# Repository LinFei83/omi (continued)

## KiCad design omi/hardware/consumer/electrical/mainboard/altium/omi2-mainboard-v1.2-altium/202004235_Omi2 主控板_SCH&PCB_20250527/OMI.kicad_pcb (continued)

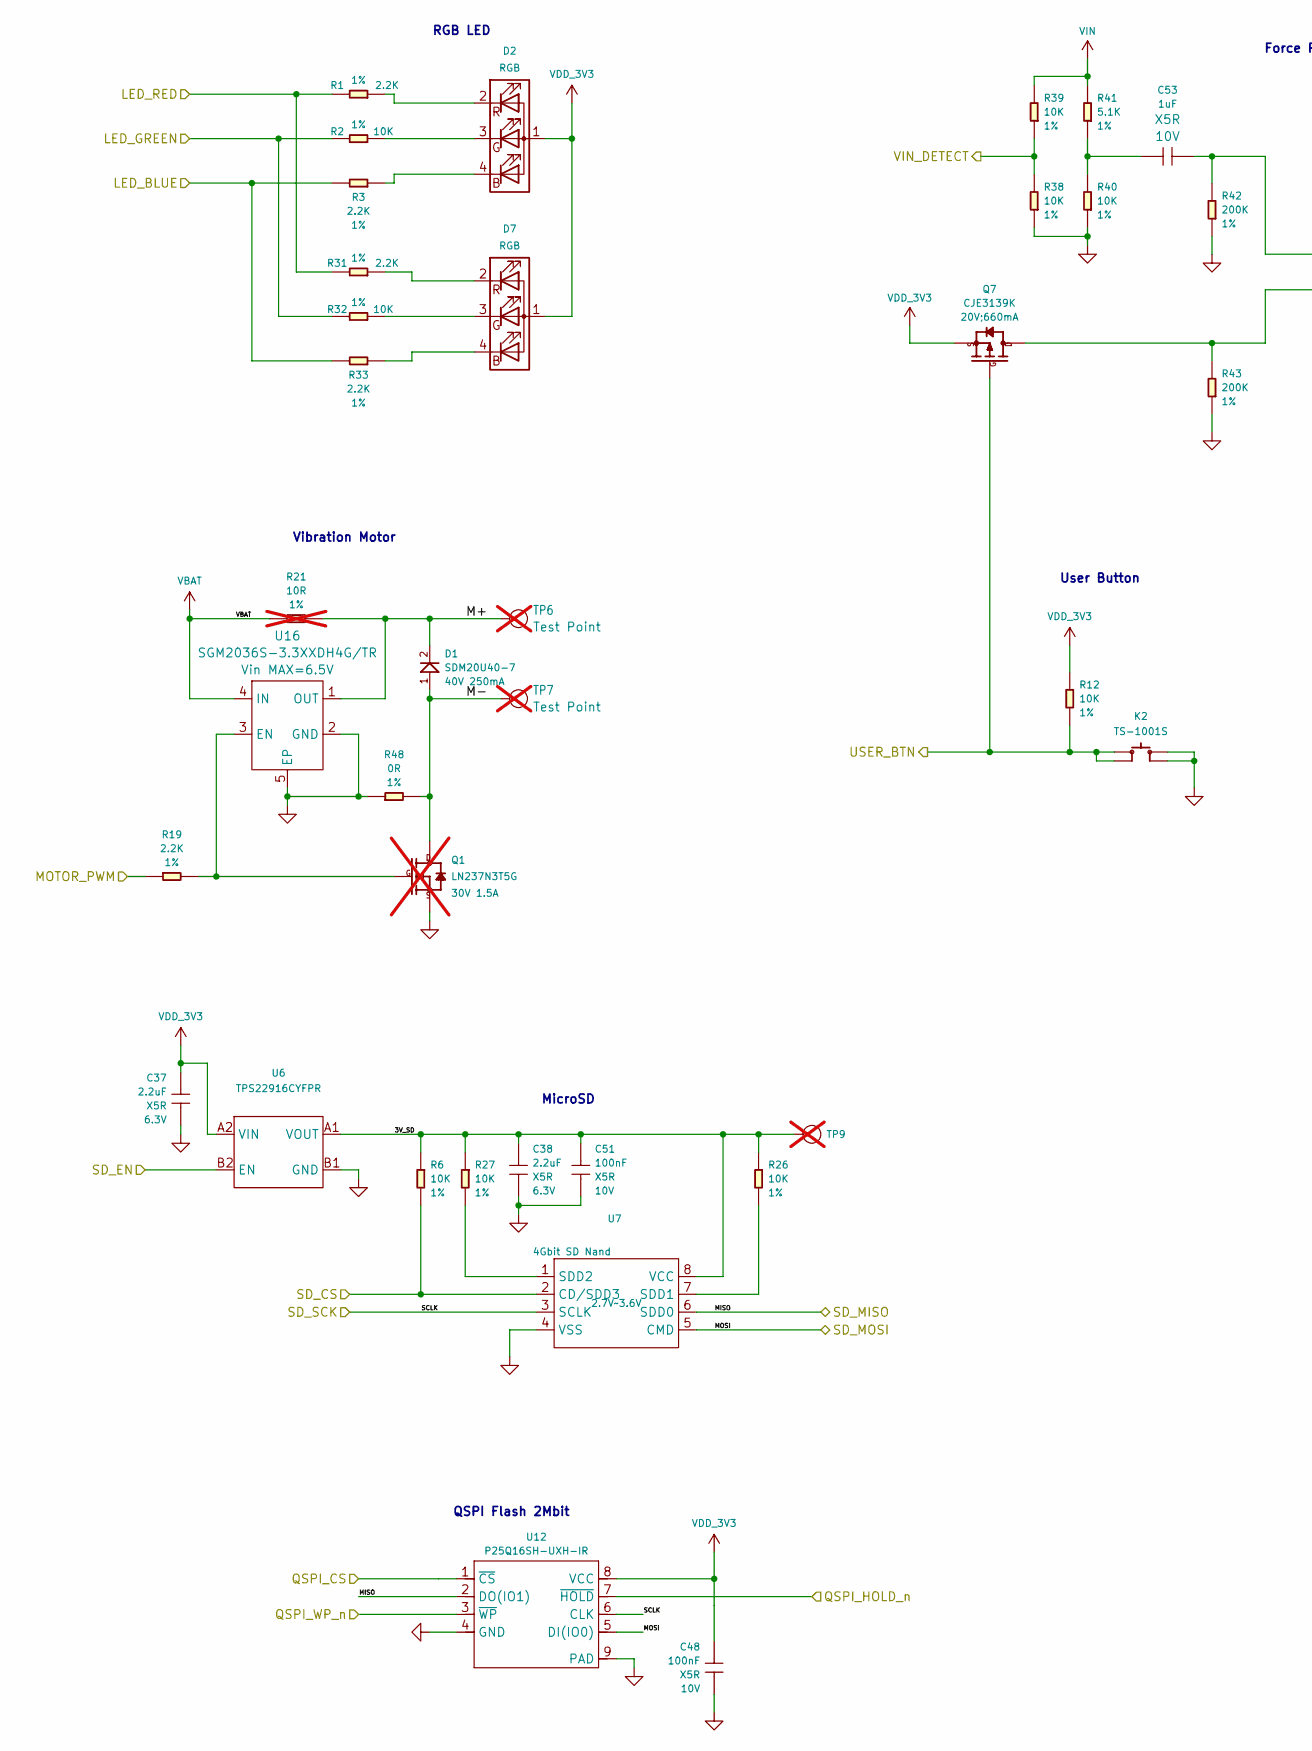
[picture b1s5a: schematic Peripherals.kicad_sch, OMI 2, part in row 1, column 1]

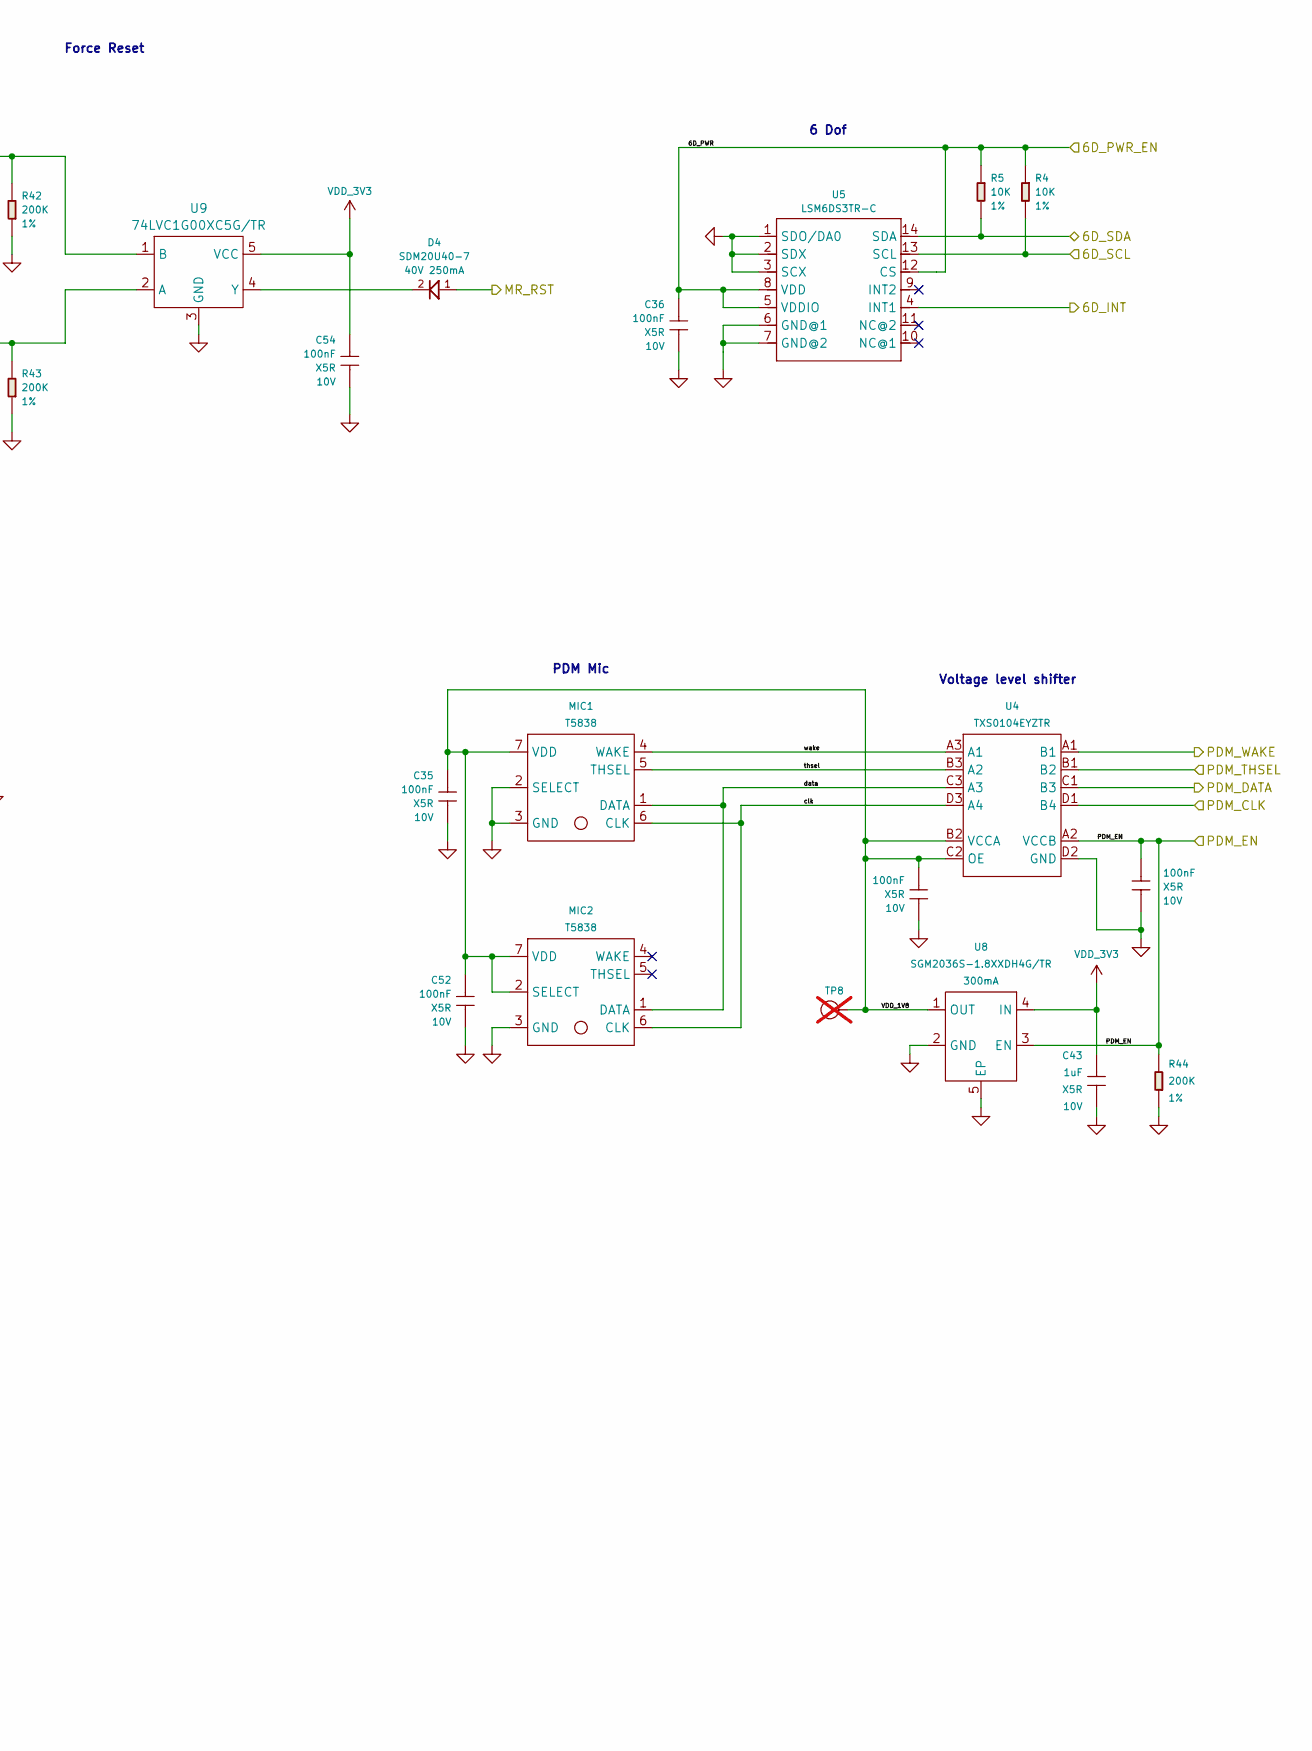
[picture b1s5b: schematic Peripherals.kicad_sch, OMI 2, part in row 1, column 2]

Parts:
C35, C36, C39, C40, C48, C51, C52, C54: 100nF; C0201; Voltage Rating 10V; MPN CC0201KRX5R6BB104
C37, C38: 2.2uF; C0201; Voltage Rating 6.3V; MPN 0201X225M6R3NT
C43, C53: 1uF; C0201; Voltage Rating 10V; MPN GRM033R61A105ME44D
D1, D4: SDM20U40-7; SOD-523; Rating 40V 250mA; MPN SDM20U40-7
D2, D7: RGB; SMD-LED-RGB-0.7X0.7X0.5MM; MPN MHPA0606RGBDT
K2: TS-1001S; SW4-SMD-2.8-2.6X1.6X0.53MM; MPN TS-1001S
MIC1, MIC2: T5838; MIC7P_0d8_3_5x2_65x0_98mm; MPN MMICT5838-00-012
Q1: LN237N3T5G; PMOS_1.0X0.6X0.35MM; Rating 30V 1.5A; MPN LN237N3T5G; not fitted
Q7: CJE3139K; SOT-523; Rating 20V;660mA; MPN CJE3139K
R1, R3, R19, R31, R33: 2.2K; R0201; Power Rating 1%; MPN RC0201FR-072K2L
R2, R4, R5, R6, R12, R26, R27, R32, R38, R39, R40: 10K; R0201; Power Rating 1%; MPN RC0201FR-0710KL
R21: 10R; R0603; Power Rating 1%; MPN RC0603FR-0710RL; not fitted
R41: 5.1K; R0201; Power Rating 1%; MPN RC0201FR-075K1L
R42, R43, R44: 200K; R0201; Power Rating 1%; MPN RC0201FR-07200KL
R48: 0R; R0201; Power Rating 1%; MPN RC0201FR-070RL
TP6, TP7: Test Point; TP-1.5X0.9MM; MPN GA30-PG05; not fitted
TP8, TP9: Test Point; TP-1X0.9MM; Part Type Test Point; not fitted
U4: TXS0104EYZTR; DSBGA12_0d5_1_89x1_39x0_625mm; MPN TXS0104EYZTR
U5: LSM6DS3TR-C; LGA14-0.5-2.5X3X0.86MM; MPN LSM6DS3TR-C
U6: TPS22916CYFPR; WLCSP4-0.4-0.77X0.77X0.33MM; MPN TPS22916CYFPR
U7: 4Gbit SD Nand; LGA8_1d27_8x6x0_85mm; Rating 2.7V~3.6V; MPN CSNP4GCR01-DPW
U8: SGM2036S-1.8XXDH4G/TR; X2SON4-0.625-1x1x0.6mm; Rating 300mA; MPN SGM2036S-1.8XXDH4G/TR
U9: 74LVC1G00XC5G/TR; SC70-5; MPN 74LVC1G00XC5G/TR
U12: P25Q16SH-UXH-IR; USON8-0.5-3X2MM; MPN P25Q16SH-UXH-IR
U16: SGM2036S-3.3XXDH4G/TR; X2SON4-0.625-1x1x0.6mm; Rating Vin MAX=6.5V; MPN SGM2036S-3.3XXDH4G/TR

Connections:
/nRF5340/P0.10/TRACEDATA1: U12.7 (~HOLD); also elsewhere on the board
/nRF5340/P0.11/TRACEDATA0: U12.1 (~CS); also elsewhere on the board
/nRF5340/P0.19: U12.3 (~WP); also elsewhere on the board
/nRF5340/P0.20: R3.2, R33.2; also elsewhere on the board
/nRF5340/P0.21: R2.2, R32.2; also elsewhere on the board
/nRF5340/P0.22: R1.2, R31.2; also elsewhere on the board
/nRF5340/P0.25/AIN4: R19.1; also elsewhere on the board
/nRF5340/P0.26/AIN5: K2.1 (A0), K2.2 (A1), Q7.1 (G), R12.2; also elsewhere on the board
/nRF5340/P1.00: U4.C1 (B3); also elsewhere on the board
/nRF5340/P1.01: U4.D1 (B4); also elsewhere on the board
/nRF5340/P1.02/TWI: U4.A1 (B1); also elsewhere on the board
/nRF5340/P1.04: C40.2, R44.2, U4.A2 (VCCB), U8.3 (EN); also elsewhere on the board
/nRF5340/P1.05: U4.B1 (B2); also elsewhere on the board
/nRF5340/P1.06: R38.2, R39.1; also elsewhere on the board
/nRF5340/P1.07: U7.3 (SCLK), U12.6 (CLK); also elsewhere on the board
/nRF5340/P1.08: U7.6 (SDD0), U12.2 (DO(IO1)); also elsewhere on the board
/nRF5340/P1.09: U7.5 (CMD), U12.5 (DI(IO0)); also elsewhere on the board
/nRF5340/P1.10: U6.B2 (EN); also elsewhere on the board
/nRF5340/P1.11: R6.2, U7.2 (CD/SDD3); also elsewhere on the board
/nRF5340/P1.12: C36.2, R4.1, R5.1, U5.5 (VDDIO), U5.8 (VDD), U5.12 (CS); also elsewhere on the board
/nRF5340/P1.13: U5.4 (INT1); also elsewhere on the board
/nRF5340/P1.14: R4.2, U5.13 (SCL); also elsewhere on the board
/nRF5340/P1.15: R5.2, U5.14 (SDA); also elsewhere on the board
/nRF5340/Peripherals/3V_SD: C38.2, C51.2, R6.1, R26.1, R27.1, TP9.1 (T), U6.A1 (VOUT), U7.8 (VCC)
/nRF5340/Peripherals/M+: D1.2, R21.2, TP6.1 (T), U16.1 (OUT)
/nRF5340/Peripherals/M-: D1.1, Q1.3 (D), R48.2, TP7.1 (T)
/nRF5340/Peripherals/VDD_1V8: C35.2, C39.2, C52.2, MIC1.7 (VDD), MIC2.2 (SELECT), MIC2.7 (VDD), TP8.1 (T), U4.B2 (VCCA), U4.C2 (OE), U8.1 (OUT)
/nRF5340/Peripherals/clk: MIC1.6 (CLK), MIC2.6 (CLK), U4.D3 (A4)
/nRF5340/Peripherals/data: MIC1.1 (DATA), MIC2.1 (DATA), U4.C3 (A3)
/nRF5340/Peripherals/thsel: MIC1.5 (THSEL), U4.B3 (A2)
/nRF5340/Peripherals/wake: MIC1.4 (WAKE), U4.A3 (A1)
/nRF5340/~RESET: D4.1; also elsewhere on the board
GND: C35.1, C36.1, C37.1, C38.1, C39.1, C40.1, C43.1, C48.1, C51.1, C52.1, C54.1, K2.3 (B0), K2.4 (B1), MIC1.2 (SELECT), MIC1.3 (GND), MIC2.3 (GND), Q1.2 (S), R38.1, R40.1, R42.1, R43.1, R44.1, R48.1, U4.D2 (GND), U5.1 (SDO/DA0), U5.2 (SDX), U5.3 (SCX), U5.6 (GND@1), U5.7 (GND@2), U6.B1 (GND), U7.4 (VSS), U8.2 (GND), U8.5 (EP), U9.3 (GND), U12.4 (GND), U12.9 (PAD), U16.2 (GND), U16.5 (EP); also elsewhere on the board
unnamed: C53.1, R40.2, R41.1
unnamed: D2.4 (BK), R3.1
unnamed: D2.3 (GK), R2.1
unnamed: D2.2 (RK), R1.1
unnamed: D7.4 (BK), R33.1
unnamed: D7.3 (GK), R32.1
unnamed: D7.2 (RK), R31.1
unnamed: Q1.1 (G), R19.2, U16.3 (EN)
unnamed: Q7.3 (D), R43.2, U9.2 (A)
unnamed: R26.2, U7.7 (SDD1)
unnamed: R27.2, U7.1 (SDD2)
unnamed: C53.2, R42.2, U9.1 (B)
unnamed: D4.2, U9.4 (Y)
VBAT: R21.1, U16.4 (IN); also elsewhere on the board
VDD_3V3: C37.2, C43.2, C48.2, C54.2, D2.1 (A), D7.1 (A), Q7.2 (S), R12.1, U6.A2 (VIN), U8.4 (IN), U9.5 (VCC), U12.8 (VCC); also elsewhere on the board
VIN: R39.2, R41.2; also elsewhere on the board

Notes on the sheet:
Force Reset
RGB LED
6 Dof
QSPI Flash 2Mbit
Vibration Motor
PDM Mic
User Button
MicroSD
Voltage level shifter

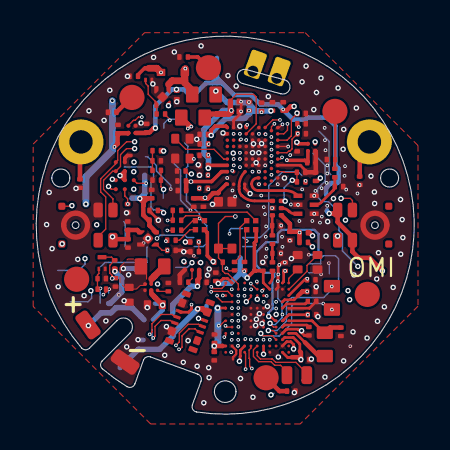
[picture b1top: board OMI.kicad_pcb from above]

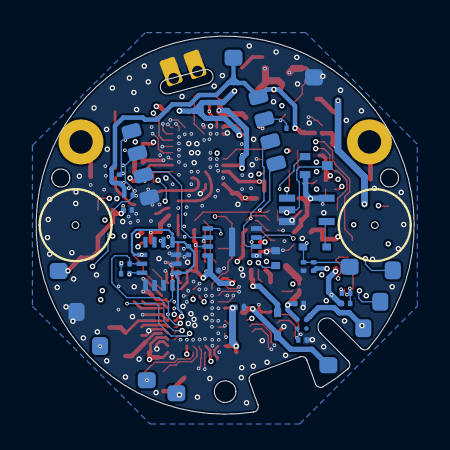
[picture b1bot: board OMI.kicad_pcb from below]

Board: 4 copper layers, 21.0 x 21.0 mm, 162 parts (36 on the bottom side), 118 nets.

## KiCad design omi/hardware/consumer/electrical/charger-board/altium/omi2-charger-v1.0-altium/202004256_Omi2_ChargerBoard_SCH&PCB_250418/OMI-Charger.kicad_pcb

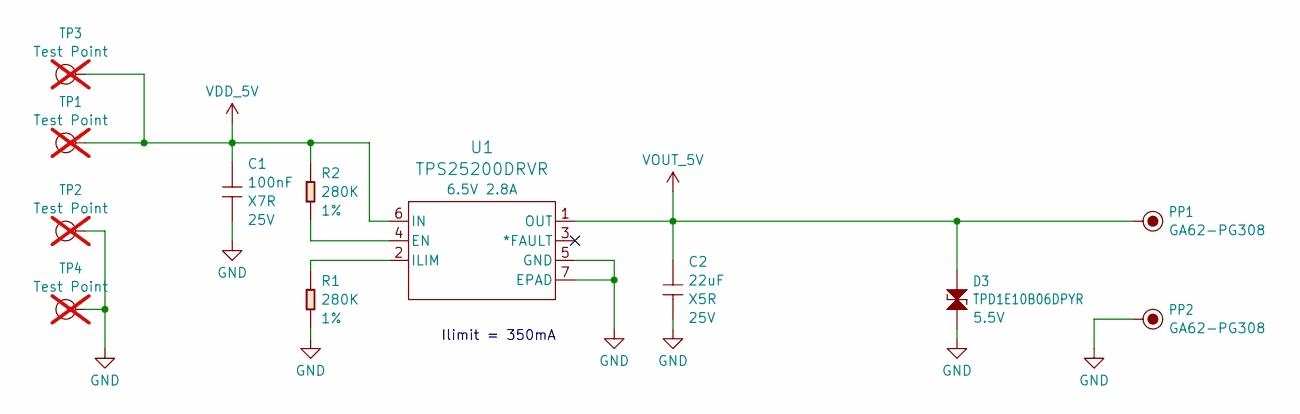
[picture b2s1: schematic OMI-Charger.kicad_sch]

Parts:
C1: 100nF; C0402; Voltage Rating 25V; MPN CC0402KRX7R8BB104
C2: 22uF; C0805; Voltage Rating 25V; MPN CC0805MKX5R8BB226
D3: TPD1E10B06DPYR; ESD-0402; Rating 5.5V; MPN TPD1E10B06DPYR
PP1, PP2: GA62-PG308; POGOPIN1_2.3X2.3X4MM; MPN GA62-PG308
R1, R2: 280K; R0402; Power Rating 1%; MPN RC0402FR-07280KL
TP1, TP2, TP3, TP4: Test Point; TP-80X40MIL; Part Type Test Point; not fitted
U1: TPS25200DRVR; DRV6-0.65-2x2x0.8mm; Rating 6.5V 2.8A; MPN TPS25200DRVR

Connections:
GND: C1.2, C2.2, D3.1, PP2.1 (T), R1.2, TP2.1 (T), TP4.1 (T), U1.5 (GND), U1.7 (EPAD)
unnamed: R2.2, U1.4 (EN)
unnamed: R1.1, U1.2 (ILIM)
VDD_5V: C1.1, R2.1, TP1.1 (T), TP3.1 (T), U1.6 (IN)
VOUT_5V: C2.1, D3.2, PP1.1 (T), U1.1 (OUT)

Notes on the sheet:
Ilimit = 350mA

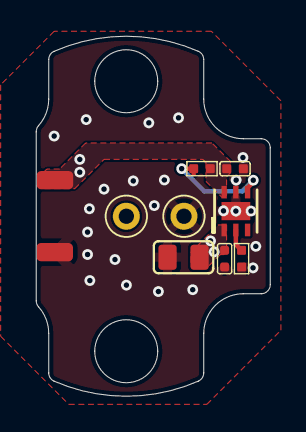
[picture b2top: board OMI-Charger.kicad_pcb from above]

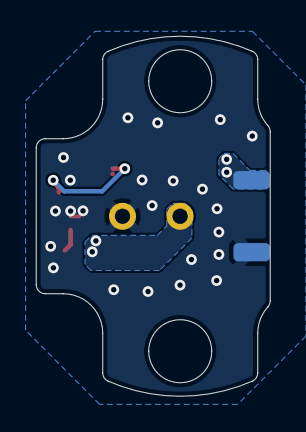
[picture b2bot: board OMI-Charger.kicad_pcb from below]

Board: 2 copper layers, 13.0 x 20.0 mm, 12 parts (2 on the bottom side), 5 nets.

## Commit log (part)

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2026-04-17 remove debug code and add SD card handler
2026-04-19 remove slow/fast advertise
2026-04-19 remove pause/resume SD card to prevent race condition
2026-04-21 chore(app): bump build to 825
2026-04-25 Defensive open-only filter at prompt rendering (greptile P1)
    _fetch_dedup_candidates already filters to open items, so the
    rendered prompt today never shows completed items. But the
    'completed' rendering at the call site was dead-but-misleading
    code: if any future caller skips the upstream filter, completed
    items would silently appear under "POTENTIALLY RELATED OPEN
    TASKS" and trick the LLM into suppressing valid new extractions.
2026-04-26 chore: consolidate changelog for v0.11.361
2026-04-26 chore: consolidate changelog for v0.11.364
2026-04-27 chore: remove fragmented docs/runbooks (#7046)
2026-04-28 android: drop ACCESS_BACKGROUND_LOCATION permission
    Removes the runtime permission to comply with Google Play's prominent
    disclosure requirement. The app only reads location while a foreground
    service of type "location" is active, which Android treats as foreground
    location access — ACCESS_FINE_LOCATION is sufficient.
2026-04-30 Rollback to use value instead of averageValue
2026-04-30 test: refactor mock patching to patch routers.developer directly for test order-independence
2026-04-30 style: apply black formatting to test_dev_api_folder_filters
    Add blank lines after `import routers.developer as _dev_router` to
    satisfy `black --line-length 120 --skip-string-normalization`, which
    is enforced by the `Lint & Format Check` workflow.
2026-04-30 ci(app): replace sort -V with portable semver comparison
    sort -V is a GNU extension; macOS BSD sort historically did not ship
    with -V support, and the script lacks set -o pipefail so a sort
    failure inside a pipeline could be swallowed by tail. Replace with
    an inline shell-arithmetic semver_gt function that uses only POSIX
    constructs available on every Codemagic runner image.
2026-05-01 Add Deployment summary for Github actions of pusher
2026-05-01 chore(app): regenerate l10n bindings for new battery_info_widget keys
    Output of \`flutter gen-l10n\` after the previous commit added 6 new
    keys to all ARB files. No hand-written changes.
2026-05-01 Add affiliate detail dialog
    Click any row in the All Affiliates tab to open a modal with full
    profile, location, social, and payout details. The dialog also fetches
    aggregate stats (pending balance, total earned/paid, total orders)
    from /api/omi/affiliates?action=detail.
2026-05-02 Update deployment summary for all services
2026-05-02 Bump tornado to 6.5.5 for 4 HIGH CVEs
    tornado: 6.4.1 -> 6.5.5 fixes:
    - CVE-2025-47287 (HIGH 7.5)
    - CVE-2026-31958 (HIGH 7.5)
    - CVE-2024-52804 (HIGH 7.5)
    - CVE-2026-35536 (HIGH 5.3)
    Verified with docker test image rebuild + unit subset all green;
2026-05-02 Bump pyasn1 to 0.6.3 for CVE-2026-30922
    pyasn1: 0.6.0 -> 0.6.3 fixes CVE-2026-30922 (HIGH 7.5).
    Verified with docker test image rebuild + unit subset all green.
2026-05-02 Add 14 missing l10n translations across 48 locales
    Keys: bulkExportInProgress, bulkExportPartial, bulkExportSuccess,
    chooseExportDestination, connectAction, connectTaskAppToExport,
    deselectAllTasksMenu, hideCompletedTasks, searchActionItems,
    selectActionItems, selectAllTasksMenu, showCompletedTasks,
    startCallRecording, startVoiceRecording
2026-05-02 Fix create_app: set uid server-side from authenticated session
    POST /v1/apps was relying on the client to populate uid in the request body.
    The Flutter client does (app/lib/pages/apps/providers/add_app_provider.dart),
    but the Next.js web portal does not — it sends only the bearer token and
    trusts the server to derive identity. The handler then stored the document
    with no uid, and get_app_details 404'd on the ownership check, making
    fresh apps unreachable to their own creator on app.omi.me.
2026-05-03 Adjust CI/CD workflow for Plugins
2026-05-03 Bump streamlit to 1.54.0 for CVE-2026-33682
    streamlit: 1.51.0 -> 1.54.0 fixes CVE-2026-33682 (CVSS 4.8,
    MEDIUM) — XSS via component-side text rendering.
    Cascade: streamlit 1.54 requires cachetools >=5.5,<7. Bumped
    cachetools 5.4.0 -> 5.5.0 (smallest version that satisfies);
    google-auth's cachetools constraint is <6,>=2.0 so 5.5.0 sits
    inside both ranges.
2026-05-04 chore: consolidate changelog for v0.11.375
2026-05-04 Override minimatch ^9.0.7 in admin dashboard
    Closes 3 HIGH CVEs flagged on omi-admin-dashboard at minimatch 9.0.5:
    - HIGH 7.5 CVE-2026-26996
    - HIGH 7.5 CVE-2026-27903
    - HIGH 7.5 CVE-2026-27904
    minimatch 9.0.5 is reached transitively via tailwindcss → sucrase →
    glob and via eslint-config-next → @typescript-eslint/parser. The
2026-05-04 app: extend summary edit to third-party app summaries
    Drops the appId == null gate added in the previous commit. The double-tap
    edit flow now works for any displayed summary; the callback receives the
    appId of the summary block being edited (null = default backend overview).
    - updateConversationSummary(conversationId, appId?, content) replaces
    updateConversationOverview
    - saveEditingSummary(appId?, content) handles both cases with the
2026-05-05 Bump pusher orjson 3.10.6 → 3.11.6
    Closes 1 HIGH CVE in the pusher service, matching backend's #7126
    pin:
    - HIGH 7.5 CVE-2025-67221
2026-05-05 Bump pusher cryptography 43.0.0 → 46.0.7
    Closes 2 CVEs in pusher, matching backend's pin progression in
    #7127 (43.0.0 → 46.0.5) and #7146 (46.0.5 → 46.0.7):
    - HIGH 6.5 CVE-2026-26007
    - MEDIUM (CVSS 9.8) CVE-2026-39892
2026-05-05 chore: consolidate changelog for v0.11.377
2026-05-05 Bump diarizer requests 2.32.5 → ~=2.33.0
    Closes 1 MEDIUM CVE in diarizer, matching backend's #7146 pin
    syntax (compatible-release within 2.33.x):
    - MEDIUM 5.5 CVE-2026-25645
2026-05-05 Bump diarizer fastapi 0.112.0 → 0.121.0 + starlette 0.37.2 → 0.49.1
    Closes 3 CVEs in diarizer, matching backend's pin progression in
    #7127 (fastapi 0.112 → 0.118 / starlette 0.37 → 0.40) and #7146
    (fastapi 0.118 → 0.121 / starlette 0.40 → 0.49.1):
    - HIGH 7.5 CVE-2024-47874 (starlette content-length DoS)
    - HIGH 7.5 CVE-2025-62727 (starlette FileResponse path traversal)
    - MEDIUM 5.3 CVE-2025-54121
2026-05-05 Migrate plugins langchain_core.pydantic_v1 → pydantic v2
    Forward-compatible code change to unblock the langchain-core 0.2 →
    1.x bump in the next commits. `langchain_core.pydantic_v1` was a
    shim that re-exported pydantic v1 classes; it was removed in
    langchain-core 1.0 along with the pydantic v1 → v2 transition.
    Two files touched:
    - plugins/_multion/router.py: `BooksToBuy` model used by
2026-05-05 Bump plugins python-dotenv 1.0.1 → 1.2.2
    Closes 1 MEDIUM CVE matching backend's #7146:
    - MEDIUM 6.6 CVE-2026-28684
2026-05-05 Bump plugins Jinja2 3.1.4 → 3.1.6
    Closes 3 MEDIUM CVEs matching backend's #7146:
    - MEDIUM CVE-2024-56201 (sandbox escape)
    - MEDIUM CVE-2024-56326 (sandbox escape)
    - MEDIUM CVE-2025-27516 (sandbox escape)
2026-05-05 Bump plugins urllib3 2.2.2 → 2.6.3
    Closes 3 HIGH CVEs matching backend's #7126:
    - HIGH 7.5 CVE-2025-66471
    - HIGH 7.5 CVE-2026-21441
    - HIGH 7.5 CVE-2025-66418
2026-05-05 Bump plugins h11 0.14.0 → 0.16.0 + httpcore 1.0.5 → 1.0.9
    Closes 1 CRITICAL CVE matching backend's #7126:
    - CRITICAL 9.1 CVE-2025-43859 (HTTP request smuggling via
    malformed chunked encoding)
    h11 and httpcore must move together (httpcore caps h11 to a
    specific minor).
2026-05-05 Bump plugins protobuf 4.25.4 → 5.29.6 + grpcio + grpcio-tools
    Closes 1 HIGH CVE matching backend's #7127:
    - HIGH 7.5 CVE-2026-0994 (protobuf parser memory corruption)
    grpcio and grpcio-tools cascade with protobuf 5.29.x (must align
    to a compatible minor for the C-extension ABI). Bumped both to
    1.66.0 to match backend.
2026-05-05 Bump plugins openai 1.37.1 → 1.109.1
    Matches backend's pin from #7149 — openai 1.109.1 is the floor
    required by langchain-openai 1.1.9 (in the next commit). Held
    below 1.1.10 to defer the openai 2.x SDK migration.
2026-05-05 Bump plugins agentops 0.2.6 → 0.4.21
    agentops 0.2.6 hard-pinned `requests==2.31.0` which blocked the
    requests bump in 81492f212. agentops 0.4.21 widens the constraint
    to `requests<3.0.0,>=2.0.0`, unblocking the resolver.
    Note: agentops is in plugins/requirements.txt but not imported by
    any plugins/.py file at present. Bumping rather than removing —
    smaller-scope change, and the dep may be loaded by a plugin not
2026-05-05 Bump plugins groq 0.11.0 → 0.37.1 (langchain-groq 1.x floor)
    langchain-groq 1.1.2 (from d68c9d85f) requires `groq>=0.30.0,<1.0.0`.
    Plugins was on groq 0.11.0 — pinned at the time of langchain-groq
    0.1.9 — which fails the new floor.
    Bumped to 0.37.1, the latest in the 0.x line (groq 1.x is held
    back by langchain-groq's <1.0.0 cap; the 1.x SDK migration is a
    separate cascade).
2026-05-05 fix(app): suppress FCM foreground notification while voice is speaking
    Companion to the prior interruption-handler fix on this branch.
    For chat-reply pushes (notification_type=plugin) the backend sends an
    FCM with both data and a notification payload. On Android in foreground
    we re-display it via _showForegroundNotification, which uses the default
    "Omi Notifications" channel sound — that chime competes with the
    in-flight voice response for audio focus and is the most common trigger
2026-05-05 l10n(ja): keep overview key as 概要 to match English source word
    The English value of the overview key is literally "Overview", not
    "Summary", so 概要 is the correct mapping. Reverting it to 概要 keeps the
    unification per English source word: summary keys all render as 要約,
    and overview renders as 概要 — no English/Japanese mismatch and no need
    for ARB metadata to explain an intentional deviation.
    Addresses greptile review on #7182.
2026-05-05 chore(l10n): apply \n fix to regenerated localizations
    Apply the same \\n -> \n correction to the generated app_localizations_*.dart
    files so the runtime strings actually contain a newline character instead of
    the literal two-character sequence backslash + n.
    This is a targeted edit limited to the affected string literals (and the doc
    comments in app_localizations.dart that quote the English source value). It
    intentionally does not include unrelated formatter rewrites that
2026-05-06 fix(app): reset _pausedByInterruption in _clearInFlightState
    interrupt() already resets the flag; _clearInFlightState() (called from
    beginResponse() at the start of every new response) did not. If a
    notification interruption begins while the previous reply is playing
    and the user immediately asks a new question, the queues get cleared
    but _pausedByInterruption stays true. When the OS later fires the
    end+pause event for the original interruption, _onInterruption sees the
2026-05-06 添加输出日志公
